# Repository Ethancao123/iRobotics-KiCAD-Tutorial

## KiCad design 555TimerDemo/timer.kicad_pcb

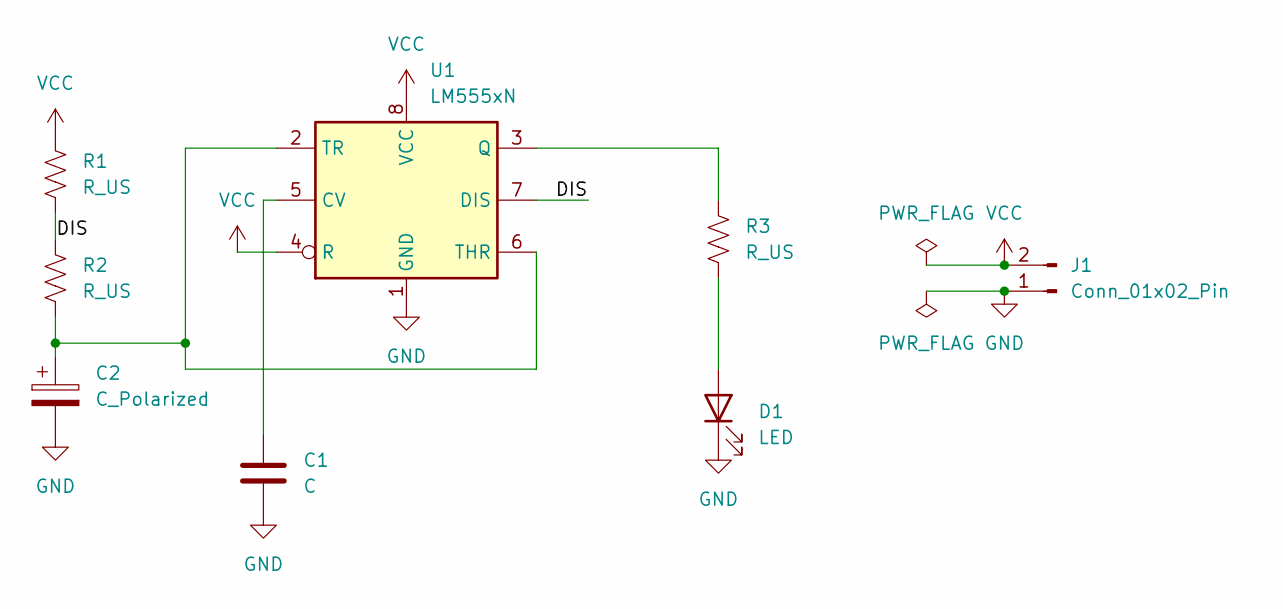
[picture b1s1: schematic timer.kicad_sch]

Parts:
C1: C; C_Disc_D5.0mm_W2.5mm_P5.00mm
C2: C_Polarized; CP_Radial_D5.0mm_P2.00mm
D1: LED; LED_D4.0mm
J1: Conn_01x02_Pin; PinHeader_1x02_P2.54mm_Vertical
R1, R2, R3: R_US; R_Axial_DIN0411_L9.9mm_D3.6mm_P15.24mm_Horizontal
U1: LM555xN; DIP-8_W7.62mm

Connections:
/DIS: R1.2, R2.1, U1.7 (DIS)
GND: C1.2, C2.2, D1.1 (K), J1.1, U1.1 (GND)
unnamed: D1.2 (A), R3.2
unnamed: C1.1, U1.5 (CV)
unnamed: R3.1, U1.3 (Q)
unnamed: C2.1, R2.2, U1.2 (TR), U1.6 (THR)
VCC: J1.2, R1.1, U1.4 (R), U1.8 (VCC)

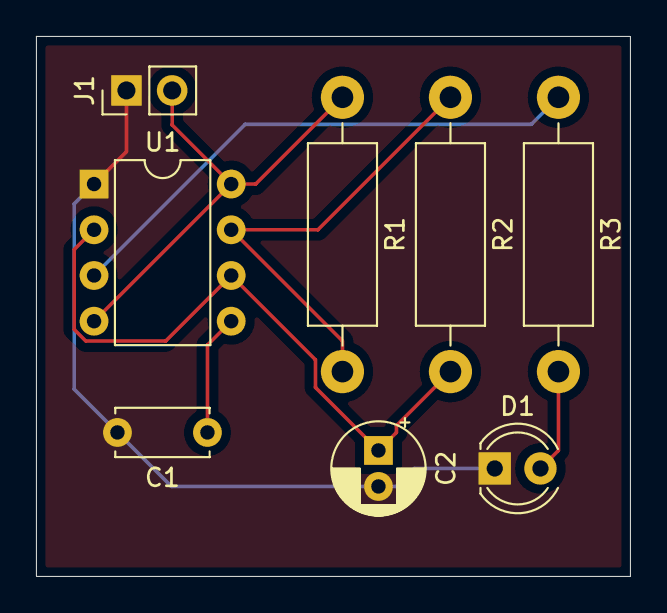
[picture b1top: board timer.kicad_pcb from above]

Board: 2 copper layers, 33.0 x 30.0 mm, 8 parts (0 on the bottom side), 7 nets.

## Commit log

2024-11-16 PCB Part 1
